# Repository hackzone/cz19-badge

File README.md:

# cz19-badge
Event badge for CampZone 2019

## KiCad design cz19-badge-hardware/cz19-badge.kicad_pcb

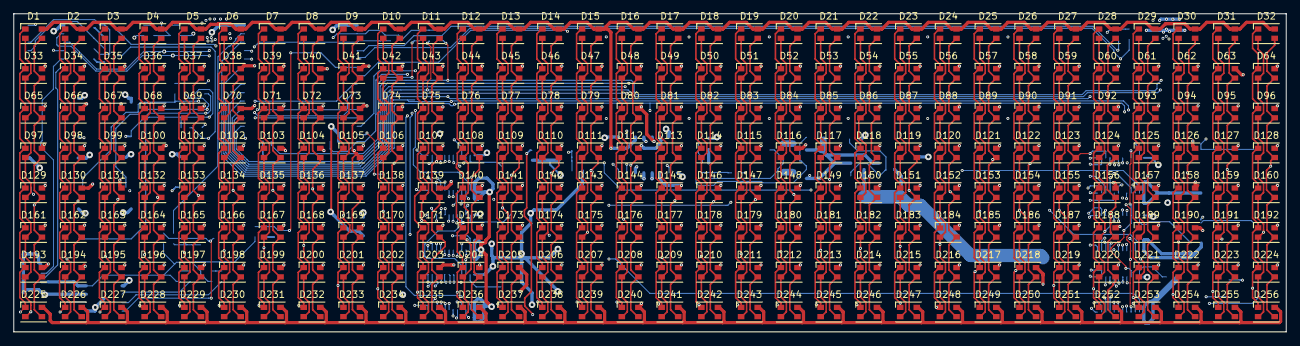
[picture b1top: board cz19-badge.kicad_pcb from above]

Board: 4 copper layers, 192.0 x 48.0 mm, 341 parts (0 on the bottom side), 167 nets.

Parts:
BT1: Battery; BatteryHolder_Keystone_1042_1x18650
C1, C2, C3, C4, C7: 100nF; C_0603_1608Metric
C5: 10uf; C_1206_3216Metric
C6: 100uf; C_Elec_4x5.8
D1, D2, D3, D4, D5, D6, D7, D8, D9, D10, D11, D12, D13, D14, D15, D16, D17, D18, D19, D20, D21, D22, D23, D24, D25, D26, D27, D28, D29, D30, D31, D32, D33, D34, D35, D36, D37, D38, D39, D40, D41, D42, D43, D44, D45, D46, D47, D48, D49, D50, D51, D52, D53, D54, D55, D56, D57, D58, D59, D60, D61, D62, D63, D64, D65, D66, D67, D68, D69, D70, D71, D72, D73, D74, D75, D76, D77, D78, D79, D80, D81, D82, D83, D84, D85, D86, D87, D88, D89, D90, D91, D92, D93, D94, D95, D96, D97, D98, D99, D100, D101, D102, D103, D104, D105, D106, D107, D108, D109, D110, D111, D112, D113, D114, D115, D116, D117, D118, D119, D120, D121, D122, D123, D124, D125, D126, D127, D128, D129, D130, D131, D132, D133, D134, D135, D136, D137, D138, D139, D140, D141, D142, D143, D144, D145, D146, D147, D148, D149, D150, D151, D152, D153, D154, D155, D156, D157, D158, D159, D160, D161, D162, D163, D164, D165, D166, D167, D168, D169, D170, D171, D172, D173, D174, D175, D176, D177, D178, D179, D180, D181, D182, D183, D184, D185, D186, D187, D188, D189, D190, D191, D192, D193, D194, D195, D196, D197, D198, D199, D200, D201, D202, D203, D204, D205, D206, D207, D208, D209, D210, D211, D212, D213, D214, D215, D216, D217, D218, D219, D220, D221, D222, D223, D224, D225, D226, D227, D228, D229, D230, D231, D232, D233, D234, D235, D236, D237, D238, D239, D240, D241, D242, D243, D244, D245, D246, D247, D248, D249, D250, D251, D252, D253, D254, D255, D256: LL-R3528RGBC-008-B; LED_Cree-PLCC4_3.2x2.8mm_CCW
D257: BLUE; LED_0603_1608Metric
D258, D260: GREEN; LED_0603_1608Metric
D259: RED; LED_0603_1608Metric
FID1, FID2, FID3, FID4: Fiducial; Fiducial_0.5mm_Mask1mm
J1: USB_B_Micro; USB_Micro-B_Molex_47346-0001
J2: Conn_02x03_Counter_Clockwise; PinSocket_2x03_P2.54mm_Vertical_SMD
J3: Hook1; TestPoint_Keystone_5019_Minature
J4: Hook2; TestPoint_Keystone_5019_Minature
JP1: SolderJumper_2_Open; SolderJumper-2_P1.3mm_Open_RoundedPad1.0x1.5mm
JP2: SolderJumper_2_Open; SolderJumper-2_P1.3mm_Bridged_RoundedPad1.0x1.5mm
Q1, Q2, Q3, Q4, Q5, Q6, Q7, Q8, Q9: AO3400 (A09T); SOT-23
R1, R2, R3, R4, R5, R6, R35: 470; R_0603_1608Metric
R7, R8, R11, R15, R16, R17, R18, R19, R20, R21, R22, R23, R24, R25, R26, R27, R28, R29, R30, R31, R32, R33, R34: 10k; R_0603_1608Metric
R9, R10, R12, R13, R14: 1k2; R_0603_1608Metric
R36: 1k; R_0603_1608Metric
SW1, SW2, SW3, SW4, SW5, SW6: SW_Push; SW_SPST_B3S-1000
U1, U2, U3, U4, U5, U6: SM16106SC; QSOP-24_3.9x8.7mm_P0.635mm
U7: TC7258E; SOIC-16_3.9x9.9mm_P1.27mm
U8: CH340C; SOIC-16_3.9x9.9mm_P1.27mm
U9: TP4056; SOIC-8-1EP_3.9x4.9mm_P1.27mm_EP2.35x2.35mm
U10: XC6206P332PR; SOT-89-3
U11: ESP32-WROOM-32D; ESP32-WROOM-32
U12: DW-01; SOT-23-6

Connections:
3V3: C2.1, D257.2, D258.2, J2.1, R15.2, R16.1, R17.2, R19.2, R20.1, R21.1, R23.1, R25.1, R26.1, R27.1, R28.1, U8.4, U8.16, U10.3, U11.2
5V_USB: D259.2, D260.2, J1.1, R11.1, R29.2, U9.4
-BATT: BT1.2, Q4.3, Q5.3
A: U7.15, U11.27
B: U7.16, U11.28
B0: U3.2, U11.13
B1: U3.22, U6.2
BTN_A: R17.1, SW5.1, U11.4
BTN_B: R19.1, SW6.1, U11.5
BTN_DOWN: JP2.1, R26.2, SW2.1, U11.12
BTN_LEFT: R27.2, SW3.1, U11.8
BTN_RIGHT: R28.2, SW4.1, U11.9
BTN_UP: R25.2, SW1.1, U11.11
C: U7.2, U11.30
CLK: U1.3, U2.3, U3.3, U4.3, U5.3, U6.3, U11.33
ESP_EN: C1.1, Q2.3, R15.1, U11.3
ESP_FLASH: JP2.2, Q1.3, R16.2, U11.25
ESP_RX: R10.2, U8.2, U11.34
ESP_TX: R9.1, U8.3, U11.35
G0: R23.2, U2.2, U11.23
G1: U2.22, U5.2
GND: C1.2, C2.2, C3.2, C4.2, C5.2, C6.2, C7.2, J1.5, J1.6, J2.2, J3.1, J4.1, JP1.1, Q3.2, Q6.2, Q8.2, R1.1, R2.1, R3.1, R4.1, R5.1, R6.1, R14.2, R18.1, R31.1, R32.1, R33.1, R34.1, SW1.2, SW2.2, SW3.2, SW4.2, SW5.2, SW6.2, U1.1, U2.1, U3.1, U4.1, U5.1, U6.1, U7.8, U8.1, U9.1, U9.3, U9.9, U10.1, U11.1, U11.15, U11.38, U12.6
GND_PROT: JP1.2, Q4.2, Q5.2, Q7.2, Q9.2, R36.1
HUB75_LAT: U1.4, U2.4, U3.4, U4.4, U5.4, U6.4, U11.31
HUB75_OE: U1.21, U2.21, U3.21, U4.21, U5.21, U6.21, U7.10, U11.36
HUB75_R0: U1.2, U11.16
unnamed: C7.1, R35.1, U12.5
unnamed: D1.1, D33.1, D65.1, D97.1, D129.1, D161.1, D193.1, D225.1, U1.5
unnamed: D1.2, D33.2, D65.2, D97.2, D129.2, D161.2, D193.2, D225.2, U2.5
unnamed: D1.3, D33.3, D65.3, D97.3, D129.3, D161.3, D193.3, D225.3, U3.5
unnamed: D1.4, D2.4, D3.4, D4.4, D5.4, D6.4, D7.4, D8.4, D9.4, D10.4, D11.4, D12.4, D13.4, D14.4, D15.4, D16.4, D17.4, D18.4, D19.4, D20.4, D21.4, D22.4, D23.4, D24.4, D25.4, D26.4, D27.4, D28.4, D29.4, D30.4, D31.4, D32.4, U7.3
unnamed: D10.1, D42.1, D74.1, D106.1, D138.1, D170.1, D202.1, D234.1, U1.14
unnamed: D10.2, D42.2, D74.2, D106.2, D138.2, D170.2, D202.2, D234.2, U2.14
unnamed: D10.3, D42.3, D74.3, D106.3, D138.3, D170.3, D202.3, D234.3, U3.14
unnamed: D33.4, D34.4, D35.4, D36.4, D37.4, D38.4, D39.4, D40.4, D41.4, D42.4, D43.4, D44.4, D45.4, D46.4, D47.4, D48.4, D49.4, D50.4, D51.4, D52.4, D53.4, D54.4, D55.4, D56.4, D57.4, D58.4, D59.4, D60.4, D61.4, D62.4, D63.4, D64.4, U7.4
unnamed: D65.4, D66.4, D67.4, D68.4, D69.4, D70.4, D71.4, D72.4, D73.4, D74.4, D75.4, D76.4, D77.4, D78.4, D79.4, D80.4, D81.4, D82.4, D83.4, D84.4, D85.4, D86.4, D87.4, D88.4, D89.4, D90.4, D91.4, D92.4, D93.4, D94.4, D95.4, D96.4, U7.5
unnamed: D4.1, D36.1, D68.1, D100.1, D132.1, D164.1, D196.1, D228.1, U1.8
unnamed: D4.2, D36.2, D68.2, D100.2, D132.2, D164.2, D196.2, D228.2, U2.8
unnamed: D4.3, D36.3, D68.3, D100.3, D132.3, D164.3, D196.3, D228.3, U3.8
unnamed: D97.4, D98.4, D99.4, D100.4, D101.4, D102.4, D103.4, D104.4, D105.4, D106.4, D107.4, D108.4, D109.4, D110.4, D111.4, D112.4, D113.4, D114.4, D115.4, D116.4, D117.4, D118.4, D119.4, D120.4, D121.4, D122.4, D123.4, D124.4, D125.4, D126.4, D127.4, D128.4, U7.6
unnamed: D5.1, D37.1, D69.1, D101.1, D133.1, D165.1, D197.1, D229.1, U1.9
unnamed: D5.2, D37.2, D69.2, D101.2, D133.2, D165.2, D197.2, D229.2, U2.9
unnamed: D5.3, D37.3, D69.3, D101.3, D133.3, D165.3, D197.3, D229.3, U3.9
unnamed: D6.1, D38.1, D70.1, D102.1, D134.1, D166.1, D198.1, D230.1, U1.10
unnamed: D6.2, D38.2, D70.2, D102.2, D134.2, D166.2, D198.2, D230.2, U2.10
unnamed: D6.3, D38.3, D70.3, D102.3, D134.3, D166.3, D198.3, D230.3, U3.10
unnamed: D7.1, D39.1, D71.1, D103.1, D135.1, D167.1, D199.1, D231.1, U1.11
unnamed: D7.2, D39.2, D71.2, D103.2, D135.2, D167.2, D199.2, D231.2, U2.11
unnamed: D7.3, D39.3, D71.3, D103.3, D135.3, D167.3, D199.3, D231.3, U3.11
unnamed: D8.1, D40.1, D72.1, D104.1, D136.1, D168.1, D200.1, D232.1, U1.12
unnamed: D8.2, D40.2, D72.2, D104.2, D136.2, D168.2, D200.2, D232.2, U2.12
unnamed: D8.3, D40.3, D72.3, D104.3, D136.3, D168.3, D200.3, D232.3, U3.12
unnamed: D9.1, D41.1, D73.1, D105.1, D137.1, D169.1, D201.1, D233.1, U1.13
unnamed: D9.2, D41.2, D73.2, D105.2, D137.2, D169.2, D201.2, D233.2, U2.13
unnamed: D9.3, D41.3, D73.3, D105.3, D137.3, D169.3, D201.3, D233.3, U3.13
unnamed: D11.1, D43.1, D75.1, D107.1, D139.1, D171.1, D203.1, D235.1, U1.15
unnamed: D11.2, D43.2, D75.2, D107.2, D139.2, D171.2, D203.2, D235.2, U2.15
unnamed: D11.3, D43.3, D75.3, D107.3, D139.3, D171.3, D203.3, D235.3, U3.15
unnamed: D12.1, D44.1, D76.1, D108.1, D140.1, D172.1, D204.1, D236.1, U1.16
unnamed: D12.2, D44.2, D76.2, D108.2, D140.2, D172.2, D204.2, D236.2, U2.16
unnamed: D12.3, D44.3, D76.3, D108.3, D140.3, D172.3, D204.3, D236.3, U3.16
unnamed: D13.1, D45.1, D77.1, D109.1, D141.1, D173.1, D205.1, D237.1, U1.17
unnamed: D13.2, D45.2, D77.2, D109.2, D141.2, D173.2, D205.2, D237.2, U2.17
unnamed: D13.3, D45.3, D77.3, D109.3, D141.3, D173.3, D205.3, D237.3, U3.17
unnamed: D14.1, D46.1, D78.1, D110.1, D142.1, D174.1, D206.1, D238.1, U1.18
unnamed: D14.2, D46.2, D78.2, D110.2, D142.2, D174.2, D206.2, D238.2, U2.18
unnamed: D14.3, D46.3, D78.3, D110.3, D142.3, D174.3, D206.3, D238.3, U3.18
unnamed: D15.1, D47.1, D79.1, D111.1, D143.1, D175.1, D207.1, D239.1, U1.19
unnamed: D15.2, D47.2, D79.2, D111.2, D143.2, D175.2, D207.2, D239.2, U2.19
unnamed: D15.3, D47.3, D79.3, D111.3, D143.3, D175.3, D207.3, D239.3, U3.19
unnamed: D16.1, D48.1, D80.1, D112.1, D144.1, D176.1, D208.1, D240.1, U1.20
unnamed: D16.2, D48.2, D80.2, D112.2, D144.2, D176.2, D208.2, D240.2, U2.20
unnamed: D16.3, D48.3, D80.3, D112.3, D144.3, D176.3, D208.3, D240.3, U3.20
unnamed: D17.1, D49.1, D81.1, D113.1, D145.1, D177.1, D209.1, D241.1, U4.5
unnamed: D17.2, D49.2, D81.2, D113.2, D145.2, D177.2, D209.2, D241.2, U5.5
unnamed: D17.3, D49.3, D81.3, D113.3, D145.3, D177.3, D209.3, D241.3, U6.5
unnamed: D18.1, D50.1, D82.1, D114.1, D146.1, D178.1, D210.1, D242.1, U4.6
unnamed: D18.2, D50.2, D82.2, D114.2, D146.2, D178.2, D210.2, D242.2, U5.6
unnamed: D18.3, D50.3, D82.3, D114.3, D146.3, D178.3, D210.3, D242.3, U6.6
unnamed: D19.1, D51.1, D83.1, D115.1, D147.1, D179.1, D211.1, D243.1, U4.7
unnamed: D19.2, D51.2, D83.2, D115.2, D147.2, D179.2, D211.2, D243.2, U5.7
unnamed: D19.3, D51.3, D83.3, D115.3, D147.3, D179.3, D211.3, D243.3, U6.7
unnamed: D20.1, D52.1, D84.1, D116.1, D148.1, D180.1, D212.1, D244.1, U4.8
unnamed: D20.2, D52.2, D84.2, D116.2, D148.2, D180.2, D212.2, D244.2, U5.8
unnamed: D20.3, D52.3, D84.3, D116.3, D148.3, D180.3, D212.3, D244.3, U6.8
unnamed: D21.1, D53.1, D85.1, D117.1, D149.1, D181.1, D213.1, D245.1, U4.9
unnamed: D21.2, D53.2, D85.2, D117.2, D149.2, D181.2, D213.2, D245.2, U5.9
unnamed: D21.3, D53.3, D85.3, D117.3, D149.3, D181.3, D213.3, D245.3, U6.9
unnamed: D22.1, D54.1, D86.1, D118.1, D150.1, D182.1, D214.1, D246.1, U4.10
unnamed: D22.2, D54.2, D86.2, D118.2, D150.2, D182.2, D214.2, D246.2, U5.10
unnamed: D22.3, D54.3, D86.3, D118.3, D150.3, D182.3, D214.3, D246.3, U6.10
unnamed: D23.1, D55.1, D87.1, D119.1, D151.1, D183.1, D215.1, D247.1, U4.11
unnamed: D23.2, D55.2, D87.2, D119.2, D151.2, D183.2, D215.2, D247.2, U5.11
unnamed: D23.3, D55.3, D87.3, D119.3, D151.3, D183.3, D215.3, D247.3, U6.11
unnamed: D24.1, D56.1, D88.1, D120.1, D152.1, D184.1, D216.1, D248.1, U4.12
unnamed: D24.2, D56.2, D88.2, D120.2, D152.2, D184.2, D216.2, D248.2, U5.12
unnamed: D24.3, D56.3, D88.3, D120.3, D152.3, D184.3, D216.3, D248.3, U6.12
unnamed: D25.1, D57.1, D89.1, D121.1, D153.1, D185.1, D217.1, D249.1, U4.13
unnamed: D25.2, D57.2, D89.2, D121.2, D153.2, D185.2, D217.2, D249.2, U5.13
unnamed: D25.3, D57.3, D89.3, D121.3, D153.3, D185.3, D217.3, D249.3, U6.13
unnamed: D26.1, D58.1, D90.1, D122.1, D154.1, D186.1, D218.1, D250.1, U4.14
unnamed: D26.2, D58.2, D90.2, D122.2, D154.2, D186.2, D218.2, D250.2, U5.14
unnamed: D26.3, D58.3, D90.3, D122.3, D154.3, D186.3, D218.3, D250.3, U6.14
unnamed: D27.1, D59.1, D91.1, D123.1, D155.1, D187.1, D219.1, D251.1, U4.15
unnamed: D27.2, D59.2, D91.2, D123.2, D155.2, D187.2, D219.2, D251.2, U5.15
unnamed: D27.3, D59.3, D91.3, D123.3, D155.3, D187.3, D219.3, D251.3, U6.15
unnamed: D28.1, D60.1, D92.1, D124.1, D156.1, D188.1, D220.1, D252.1, U4.16
unnamed: D28.2, D60.2, D92.2, D124.2, D156.2, D188.2, D220.2, D252.2, U5.16
unnamed: D28.3, D60.3, D92.3, D124.3, D156.3, D188.3, D220.3, D252.3, U6.16
unnamed: D29.1, D61.1, D93.1, D125.1, D157.1, D189.1, D221.1, D253.1, U4.17
unnamed: D29.2, D61.2, D93.2, D125.2, D157.2, D189.2, D221.2, D253.2, U5.17
unnamed: D29.3, D61.3, D93.3, D125.3, D157.3, D189.3, D221.3, D253.3, U6.17
unnamed: D30.1, D62.1, D94.1, D126.1, D158.1, D190.1, D222.1, D254.1, U4.18
unnamed: D30.2, D62.2, D94.2, D126.2, D158.2, D190.2, D222.2, D254.2, U5.18
unnamed: D30.3, D62.3, D94.3, D126.3, D158.3, D190.3, D222.3, D254.3, U6.18
unnamed: D31.1, D63.1, D95.1, D127.1, D159.1, D191.1, D223.1, D255.1, U4.19
unnamed: D31.2, D63.2, D95.2, D127.2, D159.2, D191.2, D223.2, D255.2, U5.19
unnamed: D31.3, D63.3, D95.3, D127.3, D159.3, D191.3, D223.3, D255.3, U6.19
unnamed: D32.1, D64.1, D96.1, D128.1, D160.1, D192.1, D224.1, D256.1, U4.20
unnamed: D32.2, D64.2, D96.2, D128.2, D160.2, D192.2, D224.2, D256.2, U5.20
unnamed: D32.3, D64.3, D96.3, D128.3, D160.3, D192.3, D224.3, D256.3, U6.20
unnamed: D129.4, D130.4, D131.4, D132.4, D133.4, D134.4, D135.4, D136.4, D137.4, D138.4, D139.4, D140.4, D141.4, D142.4, D143.4, D144.4, D145.4, D146.4, D147.4, D148.4, D149.4, D150.4, D151.4, D152.4, D153.4, D154.4, D155.4, D156.4, D157.4, D158.4, D159.4, D160.4, U7.11
unnamed: D2.1, D34.1, D66.1, D98.1, D130.1, D162.1, D194.1, D226.1, U1.6
unnamed: D2.2, D34.2, D66.2, D98.2, D130.2, D162.2, D194.2, D226.2, U2.6
unnamed: D2.3, D34.3, D66.3, D98.3, D130.3, D162.3, D194.3, D226.3, U3.6
unnamed: D3.1, D35.1, D67.1, D99.1, D131.1, D163.1, D195.1, D227.1, U1.7
unnamed: D3.2, D35.2, D67.2, D99.2, D131.2, D163.2, D195.2, D227.2, U2.7
unnamed: D3.3, D35.3, D67.3, D99.3, D131.3, D163.3, D195.3, D227.3, U3.7
unnamed: D161.4, D162.4, D163.4, D164.4, D165.4, D166.4, D167.4, D168.4, D169.4, D170.4, D171.4, D172.4, D173.4, D174.4, D175.4, D176.4, D177.4, D178.4, D179.4, D180.4, D181.4, D182.4, D183.4, D184.4, D185.4, D186.4, D187.4, D188.4, D189.4, D190.4, D191.4, D192.4, U7.12
unnamed: D193.4, D194.4, D195.4, D196.4, D197.4, D198.4, D199.4, D200.4, D201.4, D202.4, D203.4, D204.4, D205.4, D206.4, D207.4, D208.4, D209.4, D210.4, D211.4, D212.4, D213.4, D214.4, D215.4, D216.4, D217.4, D218.4, D219.4, D220.4, D221.4, D222.4, D223.4, D224.4, U7.13
unnamed: D225.4, D226.4, D227.4, D228.4, D229.4, D230.4, D231.4, D232.4, D233.4, D234.4, D235.4, D236.4, D237.4, D238.4, D239.4, D240.4, D241.4, D242.4, D243.4, D244.4, D245.4, D246.4, D247.4, D248.4, D249.4, D250.4, D251.4, D252.4, D253.4, D254.4, D255.4, D256.4, U7.14
unnamed: D257.1, R9.2
unnamed: D258.1, R10.1
unnamed: D259.1, R12.2
unnamed: D260.1, R13.2
unnamed: Q1.1, R7.2
unnamed: Q1.2, R8.2, U8.13
unnamed: Q2.1, R8.1
unnamed: Q2.2, R7.1, U8.14
unnamed: Q3.3, R11.2, U9.8
unnamed: Q4.1, Q5.1, R22.1
unnamed: Q6.1, Q8.1, U12.1
unnamed: Q6.3, Q7.3
unnamed: Q7.1, Q9.1, U12.3
unnamed: Q8.3, Q9.3
unnamed: R1.2, U1.23
unnamed: R2.2, U2.23
unnamed: R3.2, U3.23
unnamed: R4.2, U4.23
unnamed: R5.2, U5.23
unnamed: R6.2, U6.23
unnamed: R12.1, U9.7
unnamed: R13.1, U9.6
unnamed: R14.1, U9.2
unnamed: R18.2, U11.24
unnamed: R24.2, U11.37
unnamed: R33.2, U11.14
unnamed: R36.2, U12.2
R1: U1.22, U4.2
SCL: J2.4, R21.2, U11.29
SDA: J2.3, R20.2, U11.26
USB_DN: J1.2, U8.6
USB_DP: J1.3, U8.5
VBAT_SENSE: C4.1, R30.1, R32.2, U11.7
VCC: BT1.1, C5.1, C6.1, R22.2, R30.2, R35.2, U1.24, U2.24, U3.24, U4.24, U5.24, U6.24, U7.1, U7.7, U7.9, U9.5, U10.2
VUSB_SENSE: C3.1, R29.1, R31.2, U11.6
~CHARGE_ENABLE: Q3.1, R24.1, R34.2

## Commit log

2019-02-20 Initial fill w/ 128 LEDs + led spacing script
2019-02-21 Finished components for USB flashing, and controlling the LEDs w/ mosfet power
2019-02-24 Added transistors and bypass jumpers for DTR/RTS to schematic
2019-02-25 Fixed led sorting script ordering
2019-02-25 Added extra led columns w/ solder jumper to go back to 8x16, added RTS/DTR fets instead of diodes, added battery circuit w/ reverse polarity protection + automatic switching to USB power
2019-02-27 Added battery, organised components, layed out PCB. Working on PCB traces of LED matrix
2019-02-27 Added majority of LED traces
2019-02-27 Finalised all crucial traces
2019-03-01 Added TP4056
2019-03-01 Added lipo charging + voltage sensing
2019-03-01 Added buttons
2019-03-01 Populated entire PoC PCB
2019-03-01 Added gerbers
2019-03-02 Fixed DRC errors and placed more labels
2019-03-02 More visual fixes
2019-03-02 Added experimental touch pad to center
2019-03-02 Fixed DRC warning
2019-03-05 Added testpoint hooks
2019-03-07 Reworking LED setup to per-column non-smart LED driving
2019-03-27 Programming fets were oriented correctly before after all
2019-05-17 Added HUB75 matrix panel
2019-05-19 Working on non-smart leds
2019-05-19 Having a small panic attack due to super small real estate at 5mm pixel pitch
2019-05-20 5mm is hard
2019-05-21 Went to 6mm pixel pitch
2019-05-21 Working on tracing
2019-05-23 Finished PCB in 6mm pixel pitch (no SAO yet)
2019-05-23 Swapped left and right button
2019-05-24 Added pulldown for GPIO12 to prevent boot instability due to flash voltage (seen through EMR)
2019-06-12 Fixes: Footprint of row selector Space for vertical stacking Widen test point pads Reduce button distance Move vias away from pads
2019-06-13 Fixes: Pulldown on charging_enable Add fiducials
2019-06-16 Preparing for production
2019-07-20 Final gerbers
2019-07-20 Updating repo w/ firmware
2019-07-20 Updating firmware
2019-07-20 Added new firmware
2019-07-20 Attempting to get rid of old firmware submodule
2019-07-20 Updating firmware submodule
2019-07-20 Once more updating firmware
2019-07-20 Added firmware
2019-07-20 Added python script for making CZ19 badge compatible icons and gifs
2019-07-20 Changed python path for convert.py
2019-07-25 Made icons include 'icon = ' prefix
2019-07-31 Latest and greatest
2019-08-21 Added BoM and pdf schematics
2019-08-21 Fixed BoM filename, added package column
2022-12-24 fixed for python3 (integer diff)
    also, pixel's rgb.gif expectes x/y and height/width as tuples
2022-12-24 more portable hashbang
2022-12-24 use # modifier to print hex
2022-12-24 split lines and frames over multiple lines, so you get sane line lengths and you can actually paste the output to the python cli
